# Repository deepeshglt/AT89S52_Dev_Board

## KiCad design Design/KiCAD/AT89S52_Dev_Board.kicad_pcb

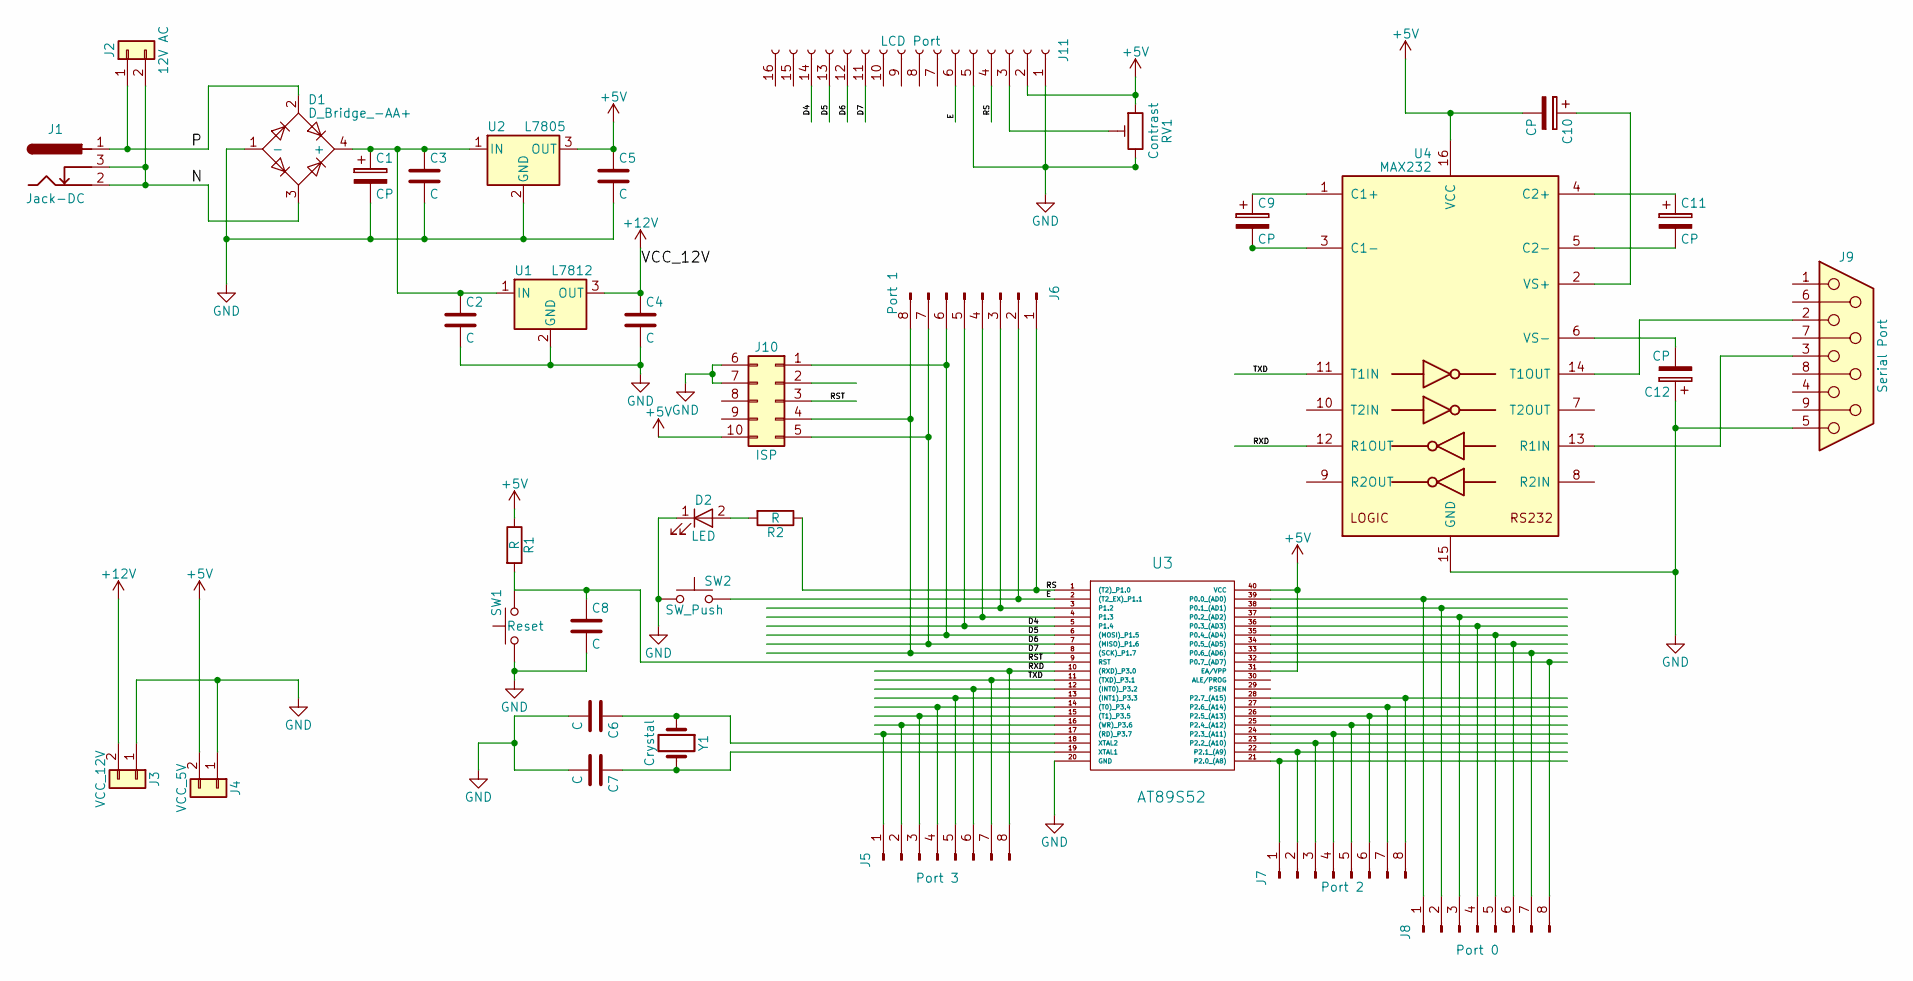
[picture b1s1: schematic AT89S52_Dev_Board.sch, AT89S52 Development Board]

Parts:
C1: CP; CP_Radial_D8.0mm_P5.00mm
C2, C6, C7, C8: C; C_Disc_D5.0mm_W2.5mm_P5.00mm
C3, C4, C5: C; C_Disc_D5.0mm_W2.5mm_P2.50mm
C9, C10, C11, C12: CP; C_Disc_D5.0mm_W2.5mm_P5.00mm
D1: D_Bridge_-AA+; Diode_Bridge_Round_D9.8mm
D2: LED; LED_D3.0mm
J1: Jack-DC; BARREL_JACK
J2: 12V AC; Socket_Strip_Straight_1x02_Pitch1.27mm
J3: VCC_12V; Socket_Strip_Straight_1x02_Pitch1.27mm
J4: VCC_5V; Socket_Strip_Straight_1x02_Pitch1.27mm
J5: Port 3; Socket_Strip_Straight_1x08_Pitch2.00mm
J6: Port 1; Socket_Strip_Straight_1x08_Pitch2.00mm
J7: Port 2; Socket_Strip_Straight_1x08_Pitch2.00mm
J8: Port 0; Socket_Strip_Straight_1x08_Pitch2.00mm
J9: Serial Port; JST_ZE_S09B-ZESK-2D_09x1.5mm_Angled
J10: ISP; Socket_Strip_Straight_2x05_Pitch2.00mm
J11: LCD Port; Socket_Strip_Straight_1x16_Pitch1.27mm
R1, R2: R; R_Axial_DIN0207_L6.3mm_D2.5mm_P7.62mm_Horizontal
RV1: Contrast; Potentiometer_Trimmer-EVM3E
SW1: Reset; SW_PUSH_6mm
SW2: SW_Push; SW_PUSH_6mm
U1: L7812; TO-126_Vertical
U2: L7805; TO-126_Vertical
U3: AT89S52; DIP-40_W15.24mm
U4: MAX232; DIP-16_W10.16mm
Y1: Crystal; Resonator-2pin_w10.0mm_h5.0mm

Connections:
+5V: C5.1, C10.2, J4.2, J10.10, J11.2, R1.1, RV1.1, U2.3 (OUT), U3.31 (EA/VPP), U3.40 (VCC), U4.16 (VCC)
+12V: C4.1, J3.2, U1.3 (OUT)
/D4: J6.5, J11.14, U3.5 (P1.4)
/D5: J6.6, J10.1, J11.13, U3.6 ((MOSI)_P1.5)
/D6: J6.7, J10.5, J11.12, U3.7 ((MISO)_P1.6)
/D7: J6.8, J10.4, J11.11, U3.8 ((SCK)_P1.7)
/E: J6.2, J11.6, SW2.2, U3.2 ((T2_EX)_P1.1)
/N: D1.3, J1.2, J1.3, J2.2
/P: D1.2, J1.1, J2.1
/RS: J6.1, J11.4, R2.1, U3.1 ((T2)_P1.0)
/RST: C8.1, J10.3, R1.2, SW1.2, U3.9 (RST)
/RXD: J5.8, U3.10 ((RXD)_P3.0), U4.12 (R1OUT)
/TXD: J5.7, U3.11 ((TXD)_P3.1), U4.11 (T1IN)
GND: C1.2, C2.2, C3.2, C4.2, C5.2, C6.2, C7.2, C8.2, C12.1, D1.1 (-), D2.1 (K), J3.1, J4.1, J9.5, J10.6, J10.7, J11.1, J11.5, RV1.3, SW1.1, SW2.1, U1.2 (GND), U2.2 (GND), U3.20 (GND), U4.15 (GND)
unnamed: C1.1, C2.1, C3.1, D1.4 (+), U1.1 (IN), U2.1 (IN)
unnamed: C6.1, U3.18 (XTAL2), Y1.1
unnamed: C7.1, U3.19 (XTAL1), Y1.2
unnamed: C9.1, U4.1 (C1+)
unnamed: C9.2, U4.3 (C1-)
unnamed: C10.1, U4.2 (VS+)
unnamed: C11.1, U4.4 (C2+)
unnamed: C11.2, U4.5 (C2-)
unnamed: C12.2, U4.6 (VS-)
unnamed: D2.2 (A), R2.2
unnamed: J5.1, U3.17 ((RD)_P3.7)
unnamed: J5.2, U3.16 ((WR)_P3.6)
unnamed: J5.3, U3.15 ((T1)_P3.5)
unnamed: J5.4, U3.14 ((T0)_P3.4)
unnamed: J5.5, U3.13 ((INT1)_P3.3)
unnamed: J5.6, U3.12 ((INT0)_P3.2)
unnamed: J6.3, U3.3 (P1.2)
unnamed: J6.4, U3.4 (P1.3)
unnamed: J7.1, U3.21 (P2.0_(A8))
unnamed: J7.2, U3.22 (P2.1_(A9))
unnamed: J7.3, U3.23 (P2.2_(A10))
unnamed: J7.4, U3.24 (P2.3_(A11))
unnamed: J7.5, U3.25 (P2.4_(A12))
unnamed: J7.6, U3.26 (P2.5_(A13))
unnamed: J7.7, U3.27 (P2.6_(A14))
unnamed: J7.8, U3.28 (P2.7_(A15))
unnamed: J8.1, U3.39 (P0.0_(AD0))
unnamed: J8.2, U3.38 (P0.1_(AD1))
unnamed: J8.3, U3.37 (P0.2_(AD2))
unnamed: J8.4, U3.36 (P0.3_(AD3))
unnamed: J8.5, U3.35 (P0.4_(AD4))
unnamed: J8.6, U3.34 (P0.5_(AD5))
unnamed: J8.7, U3.33 (P0.6_(AD6))
unnamed: J8.8, U3.32 (P0.7_(AD7))
unnamed: J9.2, U4.14 (T1OUT)
unnamed: J9.3, U4.13 (R1IN)
unnamed: J11.3, RV1.2

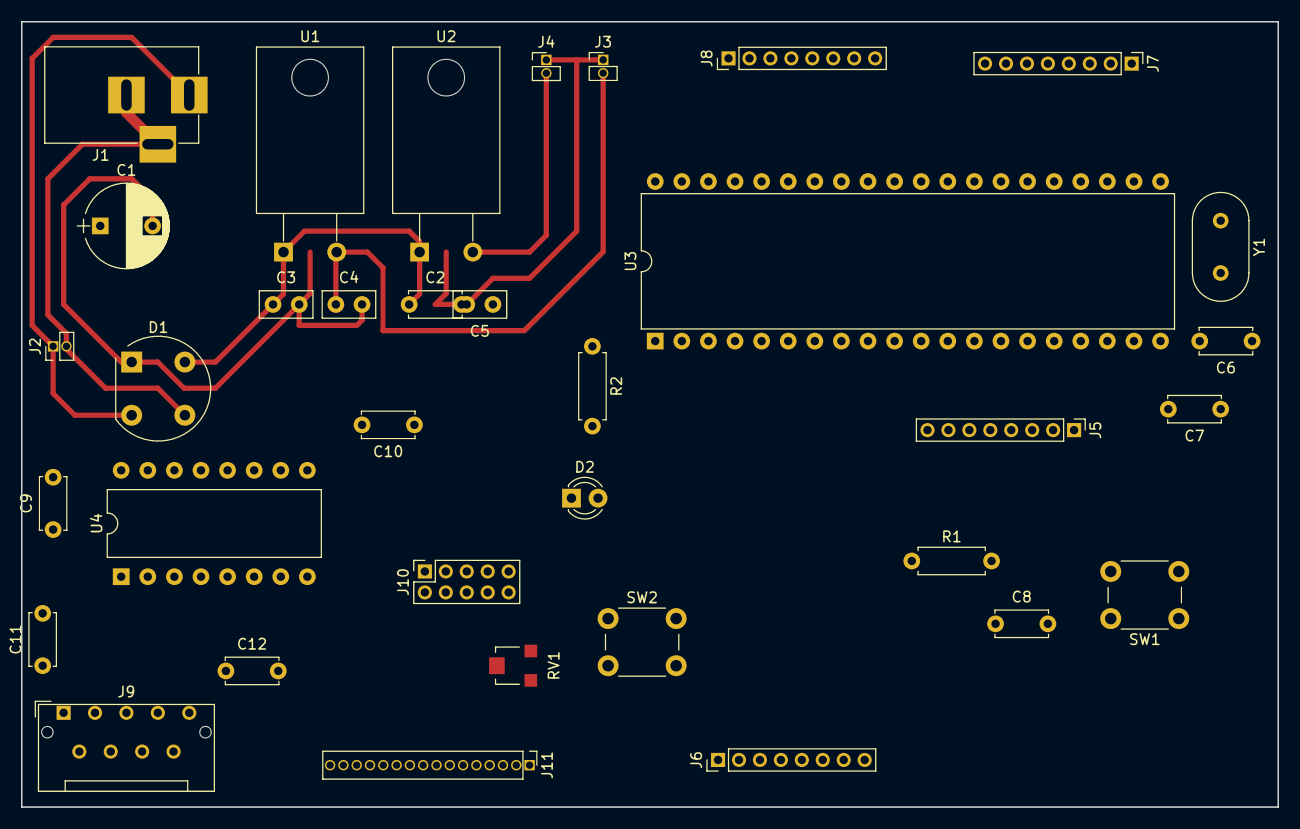
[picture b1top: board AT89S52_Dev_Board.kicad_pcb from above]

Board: 2 copper layers, 120.0 x 75.0 mm, 35 parts (0 on the bottom side), 51 nets.

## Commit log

2018-12-18 modified
